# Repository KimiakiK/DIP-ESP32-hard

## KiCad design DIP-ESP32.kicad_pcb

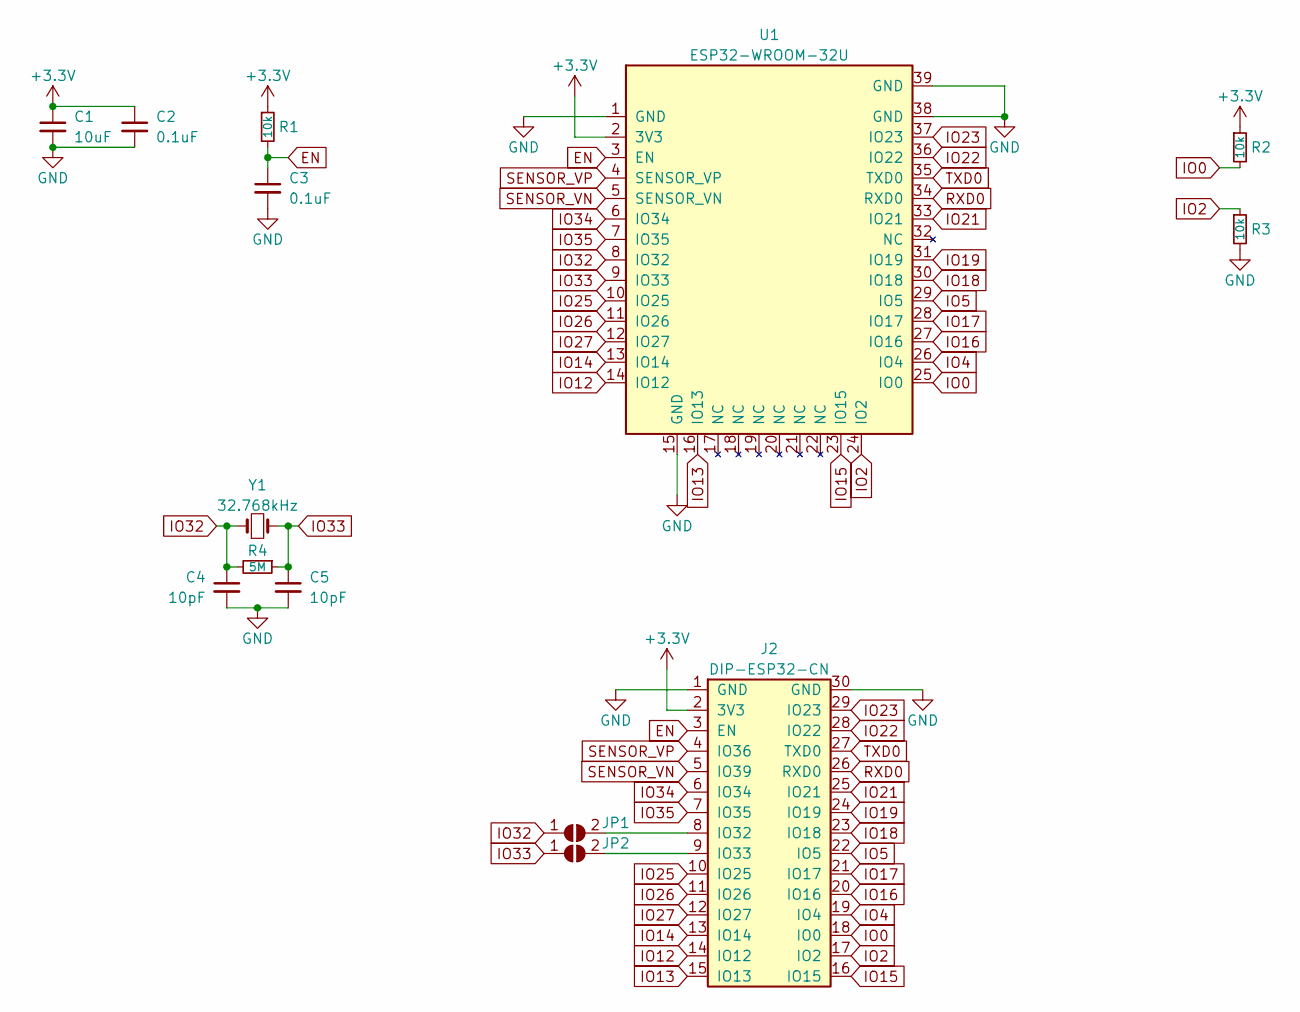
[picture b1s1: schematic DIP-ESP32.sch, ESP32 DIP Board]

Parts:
C1: 10uF; 1608Metric
C2, C3: 0.1uF; 1608Metric
C4, C5: 10pF; 1005Metric
J2: DIP-ESP32-CN
JP1, JP2: SolderJumper; SolderJumper-2_P1.3mm_Open_RoundedPad1.0x1.5mm
R1, R2, R3: 10k; 1608Metric
R4: 5M; 1608Metric
U1: ESP32-WROOM-32U; ESP32-WROOM-32
Y1: 32.768kHz; Crystal_SMD_3215-2Pin

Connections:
+3V3: C1.1, C2.1, J2.2 (3V3), R1.1, R2.1, U1.2 (3V3)
EN: C3.1, J2.3 (EN), R1.2, U1.3 (EN)
GND: C1.2, C2.2, C3.2, C4.2, C5.2, J2.1 (GND), J2.30 (GND), R3.2, U1.1 (GND), U1.15 (GND), U1.38 (GND), U1.39 (GND)
IO0: J2.18 (IO0), R2.2, U1.25 (IO0)
IO2: J2.17 (IO2), R3.1, U1.24 (IO2)
IO4: J2.19 (IO4), U1.26 (IO4)
IO5: J2.22 (IO5), U1.29 (IO5)
IO12: J2.14 (IO12), U1.14 (IO12)
IO13: J2.15 (IO13), U1.16 (IO13)
IO14: J2.13 (IO14), U1.13 (IO14)
IO15: J2.16 (IO15), U1.23 (IO15)
IO16: J2.20 (IO16), U1.27 (IO16)
IO17: J2.21 (IO17), U1.28 (IO17)
IO18: J2.23 (IO18), U1.30 (IO18)
IO19: J2.24 (IO19), U1.31 (IO19)
IO21: J2.25 (IO21), U1.33 (IO21)
IO22: J2.28 (IO22), U1.36 (IO22)
IO23: J2.29 (IO23), U1.37 (IO23)
IO25: J2.10 (IO25), U1.10 (IO25)
IO26: J2.11 (IO26), U1.11 (IO26)
IO27: J2.12 (IO27), U1.12 (IO27)
IO32: C4.1, JP1.1 (A), R4.2, U1.8 (IO32), Y1.1
IO33: C5.1, JP2.1 (A), R4.1, U1.9 (IO33), Y1.2
IO34: J2.6 (IO34), U1.6 (IO34)
IO35: J2.7 (IO35), U1.7 (IO35)
unnamed: J2.8 (IO32), JP1.2 (B)
unnamed: J2.9 (IO33), JP2.2 (B)
RXD0: J2.26 (RXD0), U1.34 (RXD0)
SENSOR_VN: J2.5 (IO39), U1.5 (SENSOR_VN)
SENSOR_VP: J2.4 (IO36), U1.4 (SENSOR_VP)
TXD0: J2.27 (TXD0), U1.35 (TXD0)

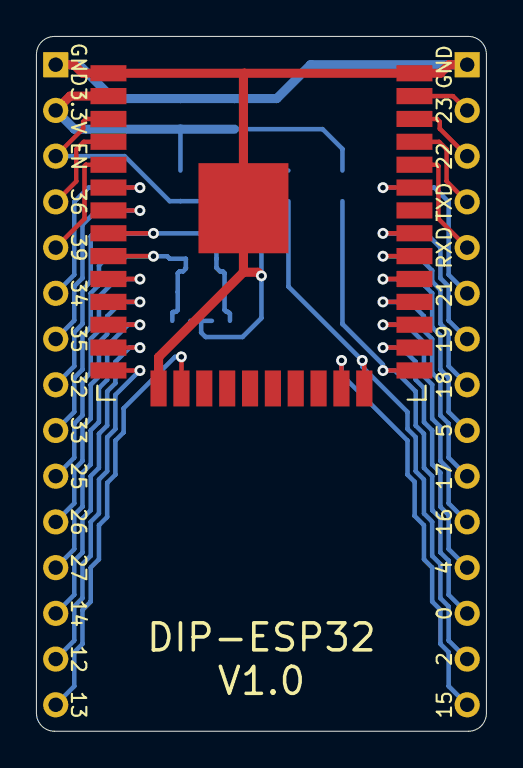
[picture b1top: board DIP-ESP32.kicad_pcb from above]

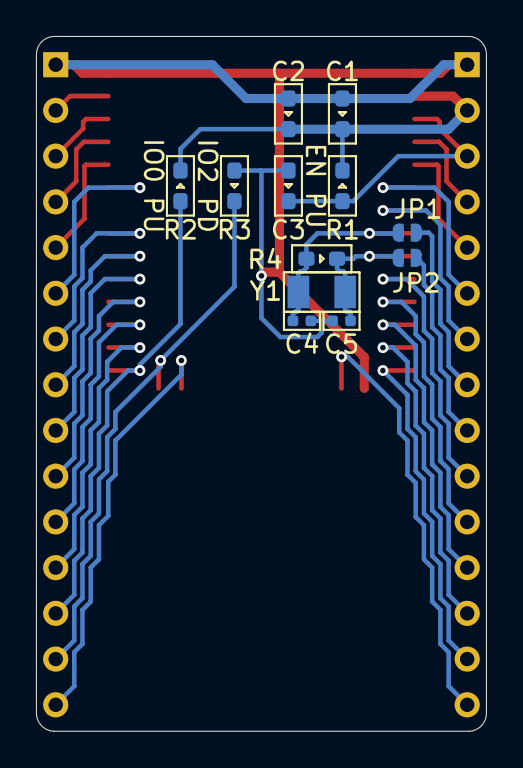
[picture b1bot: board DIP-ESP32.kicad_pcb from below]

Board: 2 copper layers, 25.0 x 38.6 mm, 14 parts (12 on the bottom side), 31 nets.

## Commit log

2021-12-01 基板 V1.0
